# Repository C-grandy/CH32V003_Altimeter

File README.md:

# CH32V003_Altimeter
A altimeter for mid to high power rocketry based around a WCH CH32V003 RISCV MCU.

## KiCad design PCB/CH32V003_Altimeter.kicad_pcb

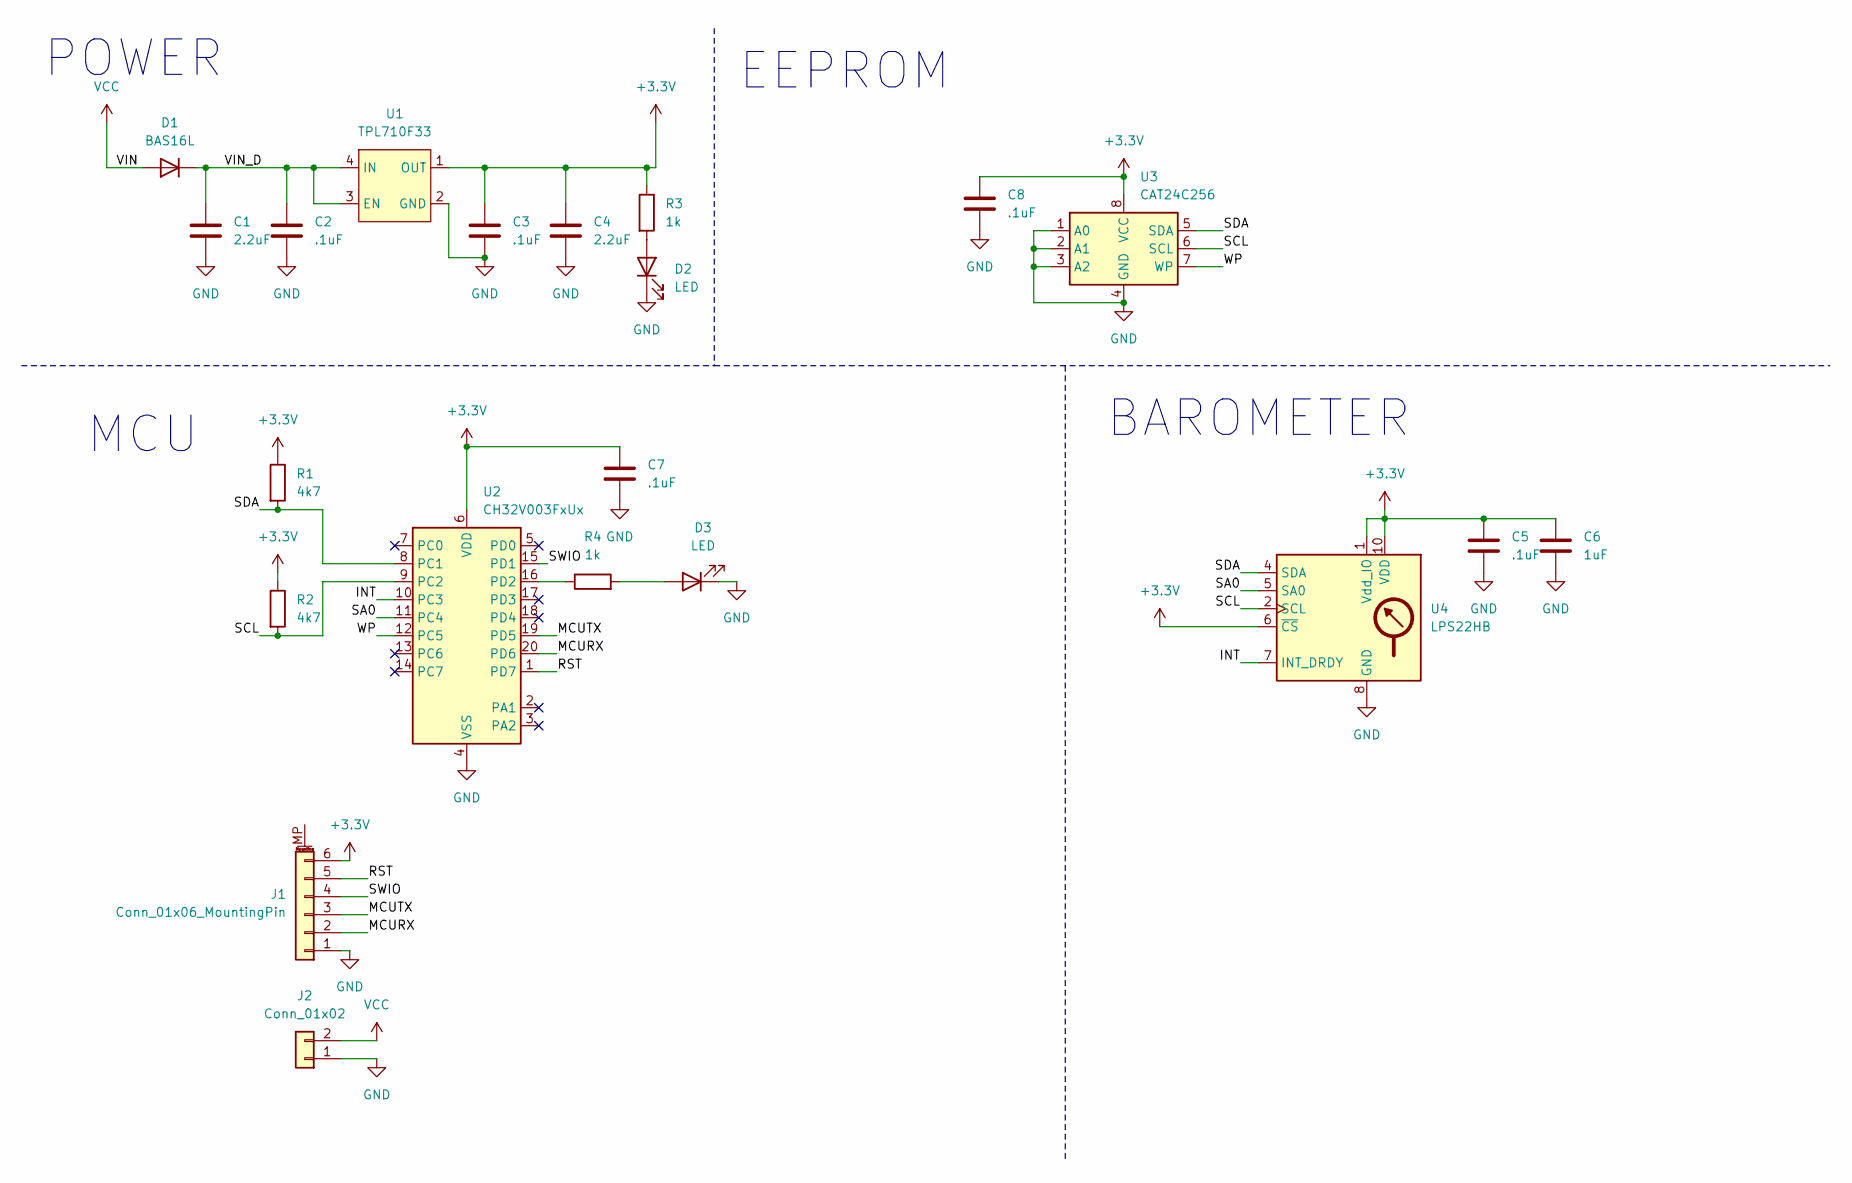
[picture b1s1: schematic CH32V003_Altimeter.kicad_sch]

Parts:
C1, C4: 2.2uF; C_0402_1005Metric
C2, C3, C5, C7, C8: .1uF; C_0402_1005Metric
C6: 1uF; C_0402_1005Metric
D1: BAS16L; D_SOD-882
D2, D3: LED; D_0402_1005Metric
J1: Conn_01x06_MountingPin; JST_SH_BM06B-SRSS-TB_1x06-1MP_P1.00mm_Vertical
J2: Conn_01x02; JST_PH_S2B-PH-K_1x02_P2.00mm_Horizontal
R1, R2: 4k7; R_0402_1005Metric
R3, R4: 1k; R_0402_1005Metric
U1: TPL710F33; UDFN-4-1EP_1x1mm_P0.65mm_EP0.48x0.48mm
U2: CH32V003FxUx; QFN-20-1EP_3x3mm_P0.4mm_EP1.65x1.65mm
U3: CAT24C256; DFN-8-1EP_2x3mm_P0.5mm_EP0.56x2.15mm
U4: LPS22HB; ST_HLGA-10_2x2mm_P0.5mm_LayoutBorder3x2y

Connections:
+3.3V: C3.1, C4.1, C5.1, C6.1, C7.1, C8.1, J1.6, R1.1, R2.1, R3.1, U1.1 (OUT), U2.6 (VDD), U3.8 (VCC), U4.1 (Vdd_IO), U4.6 (~CS), U4.10 (VDD)
/INT: U2.10 (PC3), U4.7 (INT_DRDY)
/MCURX: J1.2, U2.20 (PD6)
/MCUTX: J1.3, U2.19 (PD5)
/RST: J1.5, U2.1 (PD7)
/SA0: U2.11 (PC4), U4.5 (SA0)
/SCL: R2.2, U2.9 (PC2), U3.6 (SCL), U4.2 (SCL)
/SDA: R1.2, U2.8 (PC1), U3.5 (SDA), U4.4 (SDA)
/SWIO: J1.4, U2.15 (PD1)
/VIN_D: C1.1, C2.1, D1.1 (K), U1.3 (EN), U1.4 (IN)
/WP: U2.12 (PC5), U3.7 (WP)
GND: C1.2, C2.2, C3.2, C4.2, C5.2, C6.2, C7.2, C8.2, D2.1 (K), D3.1 (K), J1.1, J2.1, U1.2 (GND), U2.4 (VSS), U2.21 (VSS), U3.1 (A0), U3.2 (A1), U3.3 (A2), U3.4 (GND), U4.3 (GND), U4.8 (GND), U4.9 (GND)
unnamed: D2.2 (A), R3.2
unnamed: D3.2 (A), R4.2
unnamed: R4.1, U2.16 (PD2)
VCC: D1.2 (A), J2.2

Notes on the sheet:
MCU
POWER
BAROMETER
EEPROM

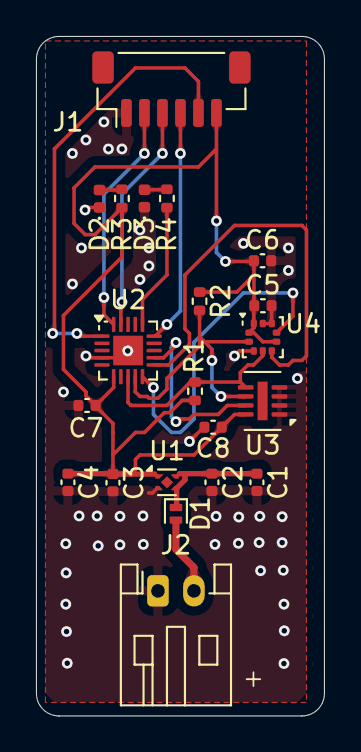
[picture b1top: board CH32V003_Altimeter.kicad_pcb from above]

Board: 2 copper layers, 16.0 x 37.8 mm, 21 parts (0 on the bottom side), 16 nets.

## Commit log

2025-09-18 Create A
